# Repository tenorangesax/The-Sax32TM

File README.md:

# The-Sax32TM
This is a simple devboard utilizing the ESP32-S3-WROOM-1 chip. Designed by me to really understand how the ESP32 works and all those little components on the front do, while also giving me a little more experience with creating devboards now.  (Being displayed at Opensauce!)

**[THE WORKING VIDEO DEMO!!](https://youtu.be/G2ZkvX7cIcQ)**

**FINAL SHOTS:**

**3D VIEWER:**
[Sax32 BOM.csv](https://github.com/user-attachments/files/30619961/Sax32.BOM.csv)

**THE SCHEMATIC:**

**PCB EDITOR:**

**BOM:**

| Id | Designator | Footprint | Quantity | Comment | Supplier and ref |
|---:|---|---|---:|---|---|
| 1 | BOOT, RST | SW_Push_SPST_NO_Alps_SKRK | 2 | SW_SPST |  |
| 2 | C1, C4 | C_0603_1608Metric | 2 | 100nf |  |
| 3 | C2, C5 | C_0603_1608Metric | 2 | 10uf |  |
| 4 | C3 | C_0603_1608Metric | 1 | 22uf |  |
| 5 | D1 | LED_0603_1608Metric | 1 | RED |  |
| 6 | D2 | LED_0603_1608Metric | 1 | GREEN |  |
| 7 | D3 | LED_0603_1608Metric | 1 | BLUE |  |
| 8 | J1, J2 | PinHeader_1x20_P2.54mm_Vertical | 2 | Conn_01x20_Pin |  |
| 9 | J3 | USB_C_Receptacle_HRO_TYPE-C-31-M-12 | 1 | USB_C_Receptacle_USB2.0_16P |  |
| 10 | R1, R2, R3, R4, R5, R6 | R_0603_1608Metric | 6 | 5.1k |  |
| 11 | U1 | SOT-223-3_TabPin2 | 1 | LD1117S33TR_SOT223 |  |
| 12 | U3 | ESP32-S3-WROOM-1 | 1 | ESP32-S3-WROOM-1 |  |

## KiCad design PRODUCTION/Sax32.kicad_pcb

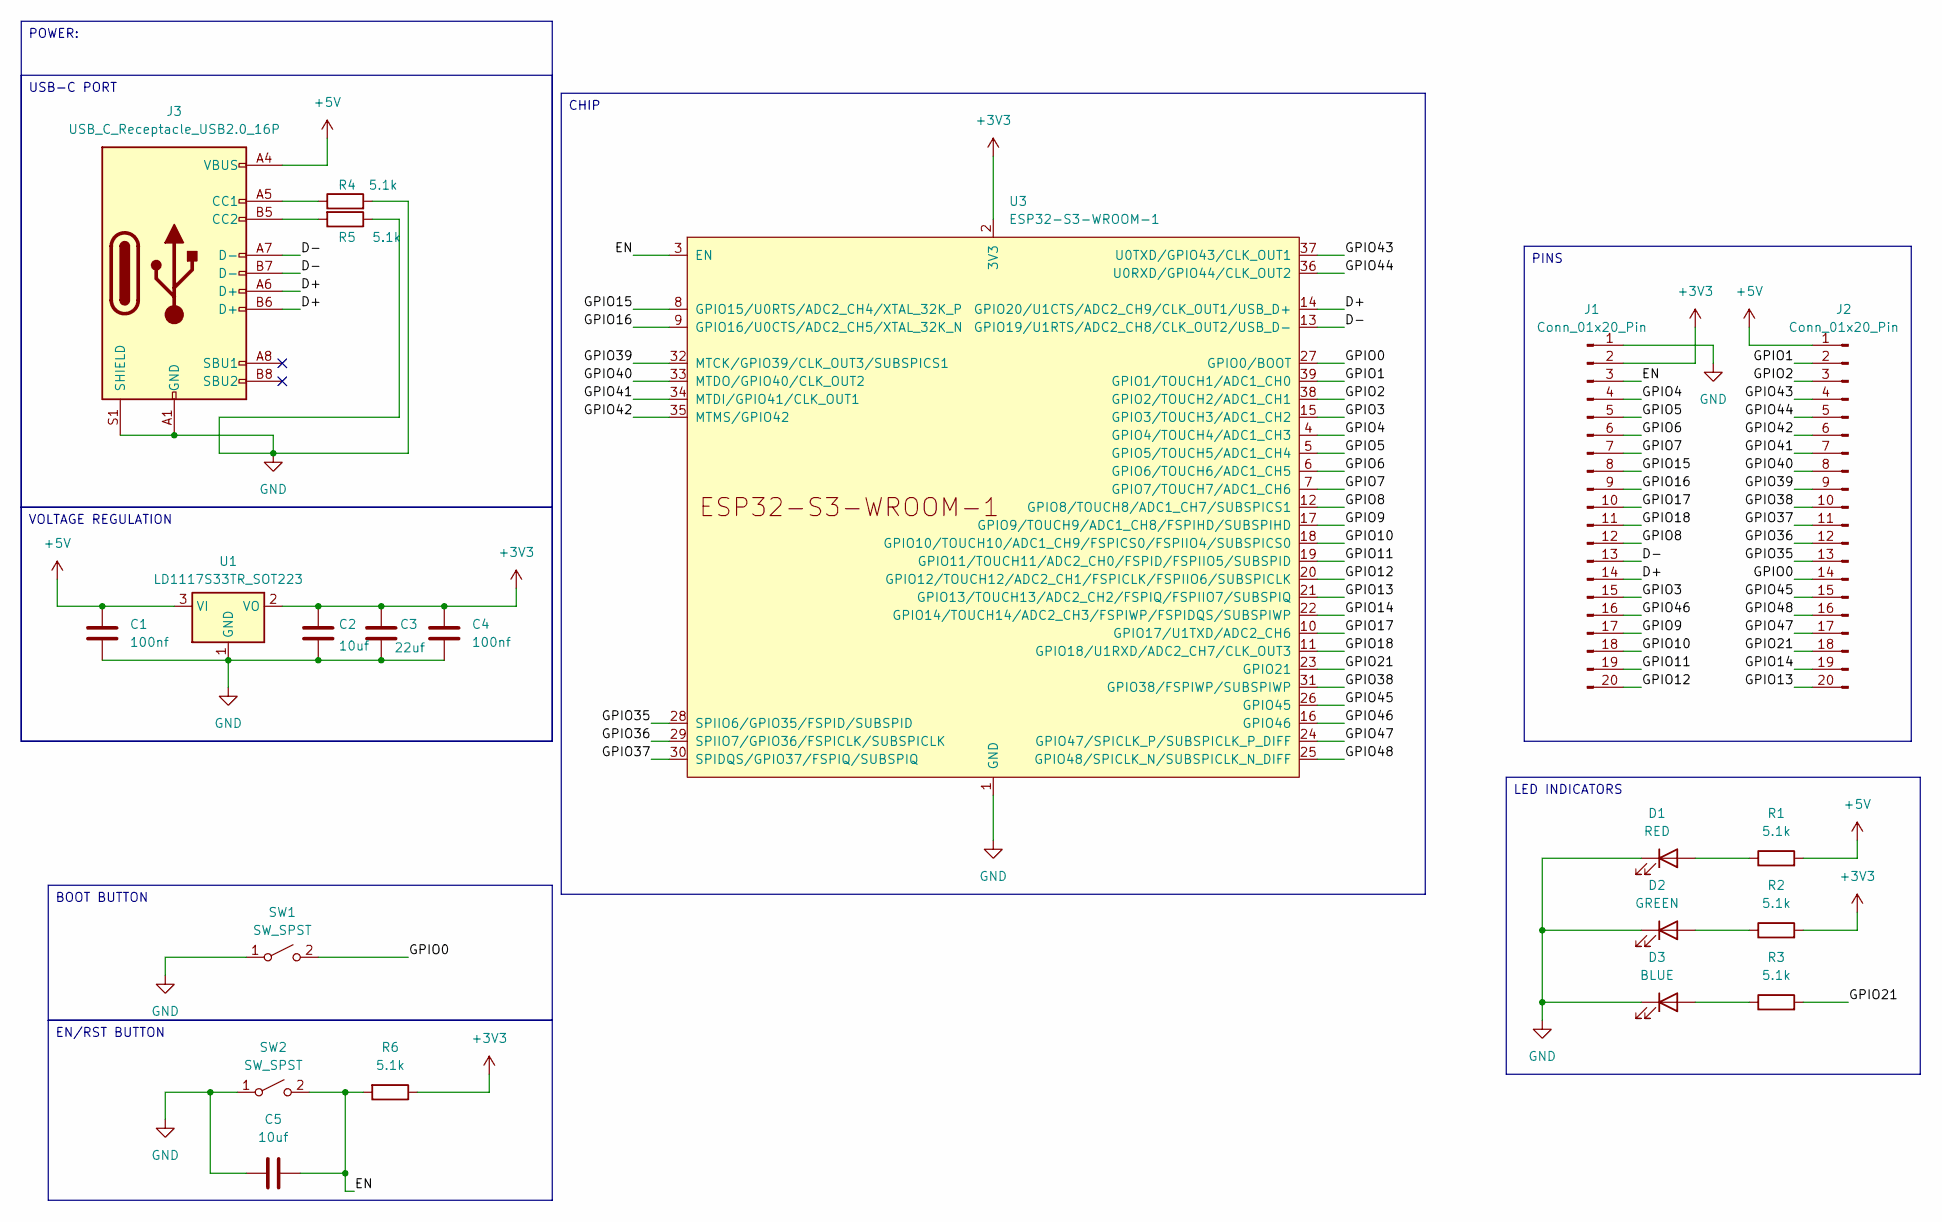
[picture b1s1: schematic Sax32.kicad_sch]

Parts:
C1, C4: 100nf; C_0603_1608Metric
C2, C5: 10uf; C_0603_1608Metric
C3: 22uf; C_0603_1608Metric
D1: RED; LED_0603_1608Metric
D2: GREEN; LED_0603_1608Metric
D3: BLUE; LED_0603_1608Metric
J1, J2: Conn_01x20_Pin; PinHeader_1x20_P2.54mm_Vertical
J3: USB_C_Receptacle_USB2.0_16P; USB_C_Receptacle_HRO_TYPE-C-31-M-12
R1, R2, R3, R4, R5, R6: 5.1k; R_0603_1608Metric
SW1, SW2: SW_SPST; SW_Push_SPST_NO_Alps_SKRK
U1: LD1117S33TR_SOT223; SOT-223-3_TabPin2
U3: ESP32-S3-WROOM-1

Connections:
+3V3: C2.1, C3.1, C4.1, J1.2, R2.2, R6.1, U1.2 (VO), U3.2 (3V3)
+5V: C1.1, J2.1, J3.A4 (VBUS), J3.A9 (VBUS), J3.B4 (VBUS), J3.B9 (VBUS), R1.2, U1.3 (VI)
/D+: J1.14, J3.A6 (D+), J3.B6 (D+), U3.14 (GPIO20/U1CTS/ADC2_CH9/CLK_OUT1/USB_D+)
/D-: J1.13, J3.A7 (D-), J3.B7 (D-), U3.13 (GPIO19/U1RTS/ADC2_CH8/CLK_OUT2/USB_D-)
/EN: C5.2, J1.3, R6.2, SW2.2 (B), U3.3 (EN); also elsewhere on the board
/GPIO0: J2.14, SW1.2 (B), U3.27 (GPIO0/BOOT); also elsewhere on the board
/GPIO1: J2.2, U3.39 (GPIO1/TOUCH1/ADC1_CH0)
/GPIO2: J2.3, U3.38 (GPIO2/TOUCH2/ADC1_CH1)
/GPIO3: J1.15, U3.15 (GPIO3/TOUCH3/ADC1_CH2)
/GPIO4: J1.4, U3.4 (GPIO4/TOUCH4/ADC1_CH3)
/GPIO5: J1.5, U3.5 (GPIO5/TOUCH5/ADC1_CH4)
/GPIO6: J1.6, U3.6 (GPIO6/TOUCH6/ADC1_CH5)
/GPIO7: J1.7, U3.7 (GPIO7/TOUCH7/ADC1_CH6)
/GPIO8: J1.12, U3.12 (GPIO8/TOUCH8/ADC1_CH7/SUBSPICS1)
/GPIO9: J1.17, U3.17 (GPIO9/TOUCH9/ADC1_CH8/FSPIHD/SUBSPIHD)
/GPIO10: J1.18, U3.18 (GPIO10/TOUCH10/ADC1_CH9/FSPICS0/FSPIIO4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)
/GPIO11: J1.19, U3.19 (GPIO11/TOUCH11/ADC2_CH0/FSPID/FSPIIO5/S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)
/GPIO12: J1.20, U3.20 (GPIO12/TOUCH12/ADC2_CH1/FSPICLK/FSPIIO6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)
/GPIO13: J2.20, U3.21 (GPIO13/TOUCH13/ADC2_CH2/FSPIQ/FSPIIO7/S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)
/GPIO14: J2.19, U3.22 (GPIO14/TOUCH14/ADC2_CH3/FSPIWP/FSPIDQS/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)
/GPIO15: J1.8, U3.8 (GPIO15/U0RTS/ADC2_CH4/XTAL_32K_P)
/GPIO16: J1.9, U3.9 (GPIO16/U0CTS/ADC2_CH5/XTAL_32K_N)
/GPIO17: J1.10, U3.10 (GPIO17/U1TXD/ADC2_CH6)
/GPIO18: J1.11, U3.11 (GPIO18/U1RXD/ADC2_CH7/CLK_OUT3)
/GPIO21: J2.18, R3.2, U3.23 (GPIO21)
/GPIO35: J2.13, U3.28 (SPIIO6/GPIO35/FSPID/SUBSPID)
/GPIO36: J2.12, U3.29 (SPIIO7/GPIO36/FSPICLK/SUBSPICLK)
/GPIO37: J2.11, U3.30 (SPIDQS/GPIO37/FSPIQ/SUBSPIQ)
/GPIO38: J2.10, U3.31 (GPIO38/FSPIWP/SUBSPIWP)
/GPIO39: J2.9, U3.32 (MTCK/GPIO39/CLK_OUT3/SUBSPICS1)
/GPIO40: J2.8, U3.33 (MTDO/GPIO40/CLK_OUT2)
/GPIO41: J2.7, U3.34 (MTDI/GPIO41/CLK_OUT1)
/GPIO42: J2.6, U3.35 (MTMS/GPIO42)
/GPIO43: J2.4, U3.37 (U0TXD/GPIO43/CLK_OUT1)
/GPIO44: J2.5, U3.36 (U0RXD/GPIO44/CLK_OUT2)
/GPIO45: J2.15, U3.26 (GPIO45)
/GPIO46: J1.16, U3.16 (GPIO46)
/GPIO47: J2.17, U3.24 (GPIO47/SPICLK_P/SUBSPICLK_P_DIFF)
/GPIO48: J2.16, U3.25 (GPIO48/SPICLK_N/SUBSPICLK_N_DIFF)
GND: C1.2, C2.2, C3.2, C4.2, C5.1, D1.1 (K), D2.1 (K), D3.1 (K), J1.1, J3.A1 (GND), J3.A12 (GND), J3.B1 (GND), J3.B12 (GND), J3.S1 (SHIELD), R4.2, R5.1, SW1.1 (A), SW2.1 (A), U1.1 (GND), U3.1 (GND), U3.40 (GND), U3.41 (GND); also elsewhere on the board
unnamed: D1.2 (A), R1.1
unnamed: D2.2 (A), R2.1
unnamed: D3.2 (A), R3.1
unnamed: J3.A5 (CC1), R4.1
unnamed: J3.B5 (CC2), R5.2

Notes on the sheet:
VOLTAGE REGULATION
PINS
POWER:
EN/RST BUTTON
LED INDICATORS
USB-C PORT
BOOT BUTTON
CHIP

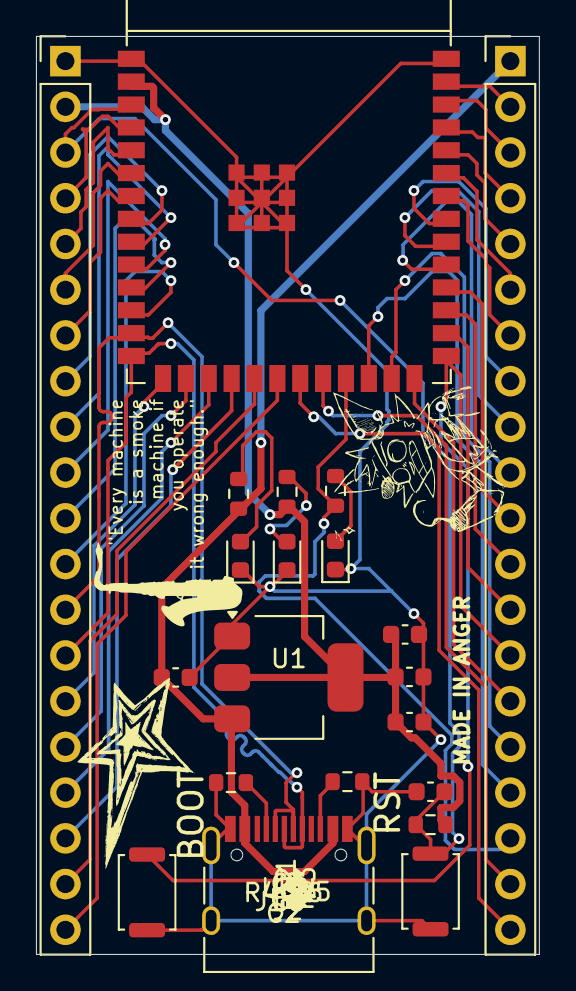
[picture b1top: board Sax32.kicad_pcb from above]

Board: 2 copper layers, 27.9 x 51.0 mm, 21 parts (0 on the bottom side), 45 nets.

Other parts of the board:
BOOT: SW_SPST; SW_Push_SPST_NO_Alps_SKRK
RST: SW_SPST; SW_Push_SPST_NO_Alps_SKRK

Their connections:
/EN: RST.2 (B); also elsewhere on the board
/GPIO0: BOOT.2 (B); also elsewhere on the board
GND: BOOT.1 (A), RST.1 (A); also elsewhere on the board

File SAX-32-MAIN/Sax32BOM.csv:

Id,Designator,Footprint,Quantity,Comment,Supplier and ref
1,"BOOT, RST",SW_Push_SPST_NO_Alps_SKRK,2,SW_SPST,
2,"C1, C4",C_0603_1608Metric,2,100nf,
3,"C2, C5",C_0603_1608Metric,2,10uf,
4,C3,C_0603_1608Metric,1,22uf,
5,D1,LED_0603_1608Metric,1,RED,
6,D2,LED_0603_1608Metric,1,GREEN,
7,D3,LED_0603_1608Metric,1,BLUE,
8,"J1, J2",PinHeader_1x20_P2.54mm_Vertical,2,Conn_01x20_Pin,
9,J3,USB_C_Receptacle_HRO_TYPE-C-31-M-12,1,USB_C_Receptacle_USB2.0_16P,
10,"R1, R2, R3, R4, R5, R6",R_0603_1608Metric,6,5.1k,
11,U1,SOT-223-3_TabPin2,1,LD1117S33TR_SOT223,
12,U3,ESP32-S3-WROOM-1,1,ESP32-S3-WROOM-1,

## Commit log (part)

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2026-06-15 Create sdfsfs
2026-06-17 Create sfd
2026-06-17 Rename Sax32 - Sax32.csv.csv to Sax32BOM.csv
